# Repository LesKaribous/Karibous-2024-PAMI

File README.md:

# Karibous-2024-PAMI
Hardware pour les Petits Automates Mobiles Indépendants de la Coupe de France de Robotique 2024

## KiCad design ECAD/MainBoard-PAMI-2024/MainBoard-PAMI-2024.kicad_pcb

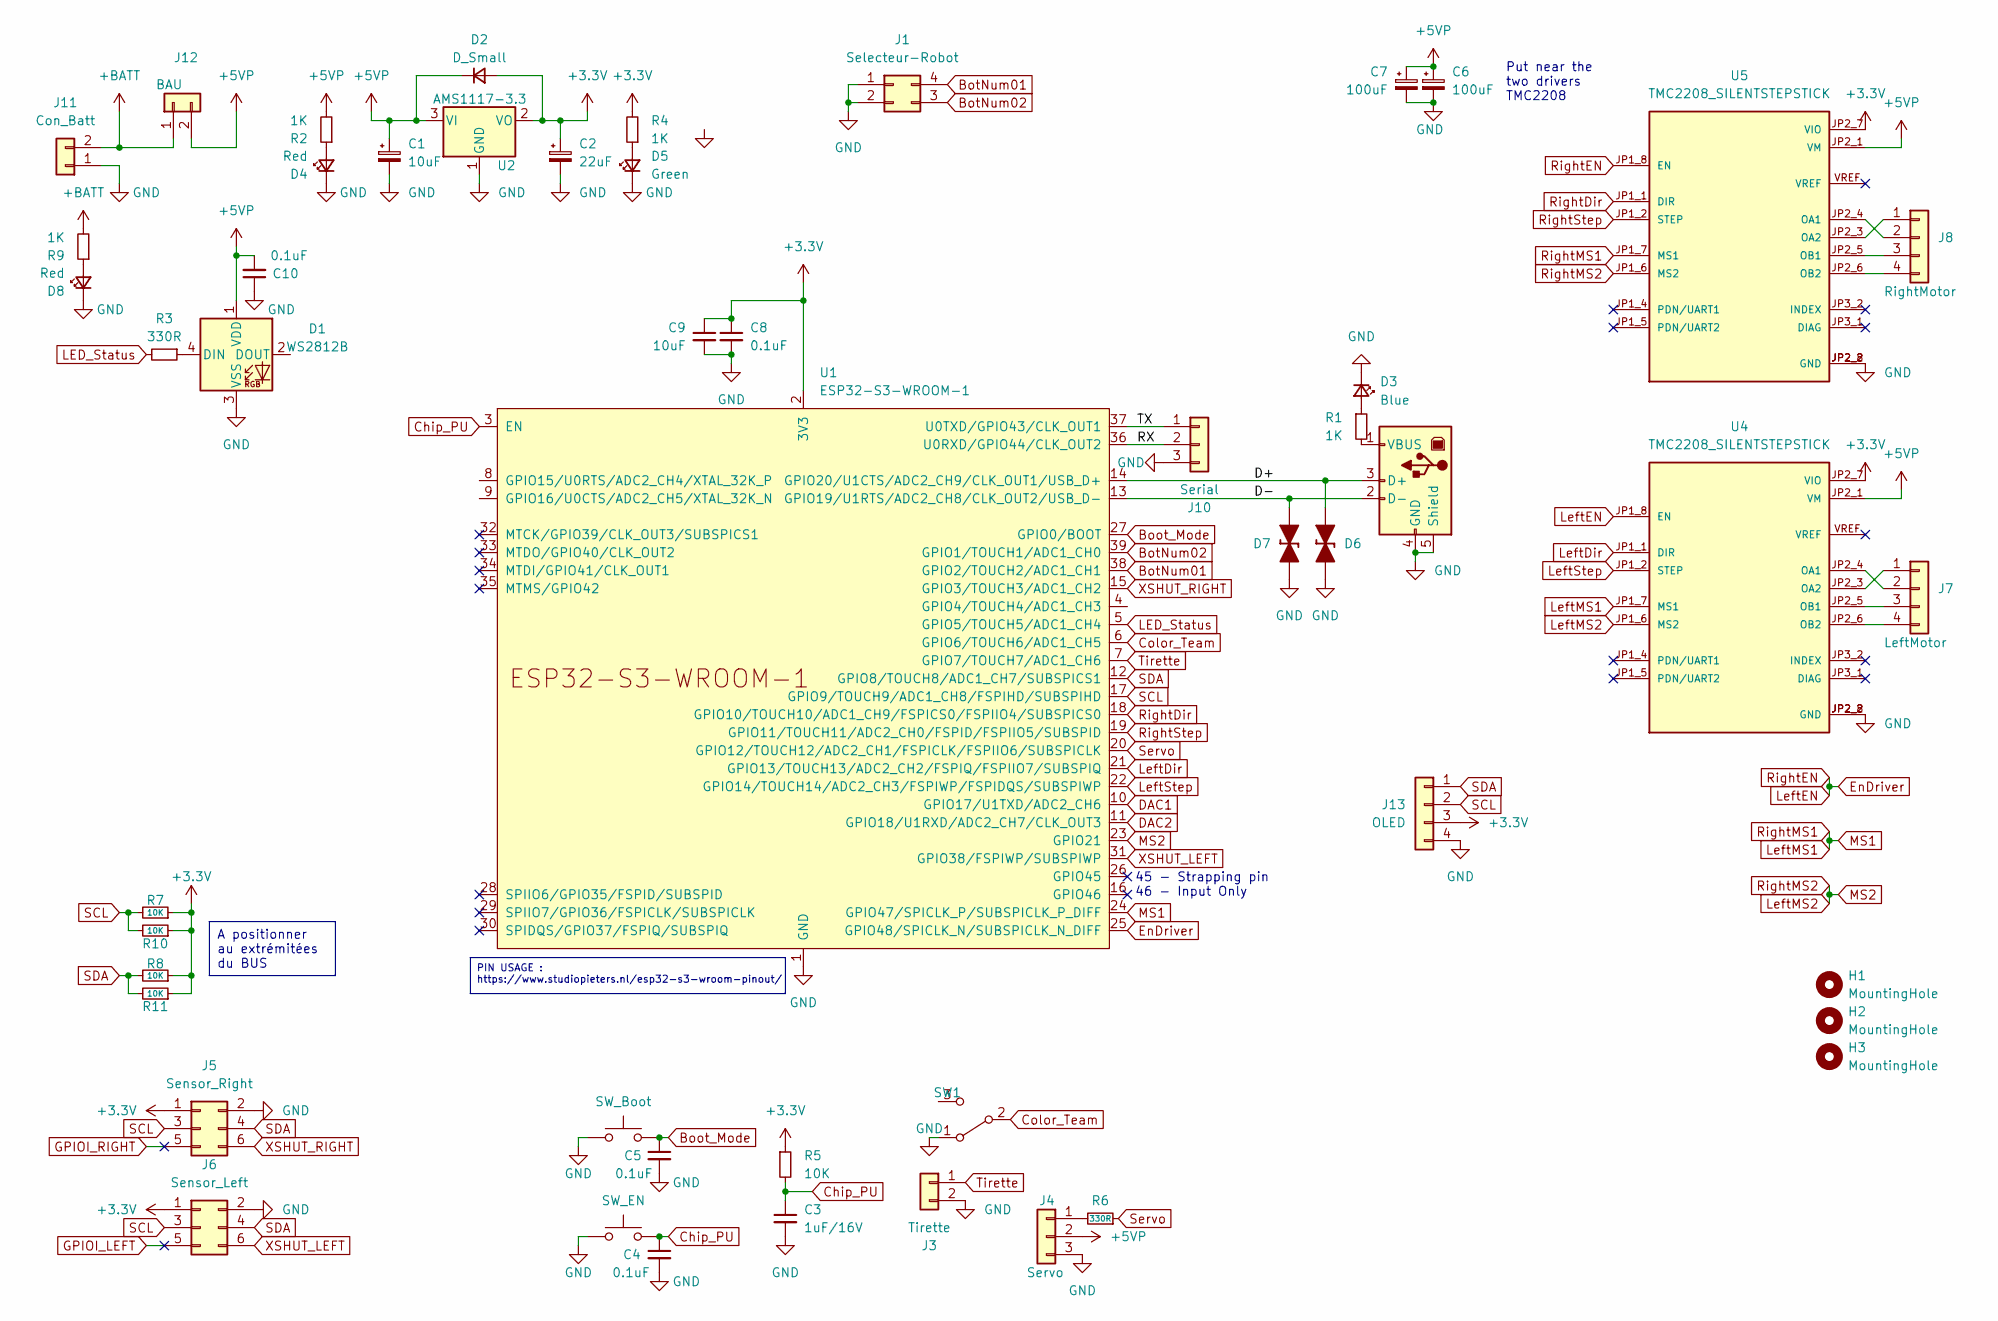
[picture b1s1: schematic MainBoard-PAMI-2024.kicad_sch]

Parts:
C1: 10uF; CP_Elec_5x5.4
C2: 22uF; CP_EIA-3528-12_Kemet-T_Pad1.50x2.35mm_HandSolder
C3: 1uF/16V; C_1206_3216Metric
C4, C5, C10: 0.1uF; C_1206_3216Metric
C6, C7: 100uF; CP_Radial_D8.0mm_P3.80mm
C8: 0.1uF; C_1206_3216Metric_Pad1.33x1.80mm_HandSolder
C9: 10uF; C_1206_3216Metric_Pad1.33x1.80mm_HandSolder
D1: WS2812B; LED_WS2812B_PLCC4_5.0x5.0mm_P3.2mm
D2: D_Small; D_SMA_Handsoldering
D3: Blue; LED_1206_3216Metric
D4, D8: Red; LED_1206_3216Metric
D5: Green; LED_1206_3216Metric
D6, D7: D_TVS_Bidirectional_Generic; D_SOD-523
H1, H2, H3: MountingHole; MountingHole_3.2mm_M3
J1: Selecteur-Robot; PinHeader_2x02_P2.54mm_Vertical
J2: USB_B; USB_B_Lumberg_2411_02_Horizontal
J3: Tirette; Molex_KK-254_AE-6410-02A_1x02_P2.54mm_Vertical
J4: Servo; PinHeader_1x03_P2.54mm_Vertical
J5: Sensor_Right; IDC-Header_2x03_P2.54mm_Vertical
J6: Sensor_Left; IDC-Header_2x03_P2.54mm_Vertical
J7: LeftMotor; PinHeader_1x04_P2.54mm_Vertical
J8: RightMotor; PinHeader_1x04_P2.54mm_Vertical
J10: Serial; PinHeader_1x03_P2.54mm_Vertical
J11: Con_Batt; AMASS_XT30U-F_1x02_P5.0mm_Vertical
J12: BAU; Molex_KK-396_A-41791-0002_1x02_P3.96mm_Vertical
J13: OLED; Molex_KK-254_AE-6410-04A_1x04_P2.54mm_Vertical
R1, R2, R4, R9: 1K; R_1206_3216Metric_Pad1.30x1.75mm_HandSolder
R3, R6: 330R; R_1206_3216Metric_Pad1.30x1.75mm_HandSolder
R5, R7, R8, R10, R11: 10K; R_1206_3216Metric_Pad1.30x1.75mm_HandSolder
SW1: SW_SPDT; SK-12D10 1P2T
SWBoot1: SW_Boot; SW_SPST_CK_RS282G05A3
SWEn1: SW_EN; SW_SPST_CK_RS282G05A3
U1: ESP32-S3-WROOM-1
U2: AMS1117-3.3; SOT-223-3_TabPin2
U4, U5: TMC2208_SILENTSTEPSTICK; MODULE_TMC2208_SILENTSTEPSTICK

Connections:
+3.3V: C2.1, C8.1, C9.1, D2.2 (A), J5.1, J6.1, J13.3, R4.2, R5.1, R7.1, R8.1, R10.1, R11.1, U1.2 (3V3), U2.2 (VO), U4.JP2_7 (VIO), U5.JP2_7 (VIO)
+5VP: C1.1, C6.1, C7.1, C10.2, D1.1 (VDD), D2.1 (K), J4.2, J12.2, R2.2, U2.3 (VI), U4.JP2_1 (VM), U5.JP2_1 (VM)
+BATT: J11.2, J12.1, R9.2
/D+: D6.2 (A), J2.3 (D+), U1.14 (GPIO20/U1CTS/ADC2_CH9/CLK_OUT1/USB_D+)
/D-: D7.2 (A), J2.2 (D-), U1.13 (GPIO19/U1RTS/ADC2_CH8/CLK_OUT2/USB_D-)
/RX: J10.2, U1.36 (U0RXD/GPIO44/CLK_OUT2)
/TX: J10.1, U1.37 (U0TXD/GPIO43/CLK_OUT1)
Boot_Mode: C5.1, SWBoot1.2, U1.27 (GPIO0/BOOT)
BotNum01: J1.4, U1.38 (GPIO2/TOUCH2/ADC1_CH1)
BotNum02: J1.3, U1.39 (GPIO1/TOUCH1/ADC1_CH0)
Chip_PU: C3.1, C4.1, R5.2, SWEn1.2, U1.3 (EN)
Color_Team: SW1.2 (B), U1.6 (GPIO6/TOUCH6/ADC1_CH5)
DAC1: U1.10 (GPIO17/U1TXD/ADC2_CH6)
DAC2: U1.11 (GPIO18/U1RXD/ADC2_CH7/CLK_OUT3)
EnDriver: U1.25 (GPIO48/SPICLK_N/SUBSPICLK_N_DIFF), U4.JP1_8 (EN), U5.JP1_8 (EN)
GND: C1.2, C2.2, C3.2, C4.2, C5.2, C6.2, C7.2, C8.2, C9.2, C10.1, D1.3 (VSS), D3.1 (K), D4.1 (K), D5.1 (K), D6.1 (K), D7.1 (K), D8.1 (K), J1.1, J1.2, J2.4 (GND), J2.5 (Shield), J3.2, J4.3, J5.2, J6.2, J10.3, J11.1, J13.4, SW1.1 (A), SWBoot1.1, SWEn1.1, U1.1 (GND), U1.40 (GND), U1.41 (GND), U2.1 (GND), U4.JP2_2 (GND), U4.JP2_8 (GND), U5.JP2_2 (GND), U5.JP2_8 (GND)
GPIOI_LEFT: J6.5
GPIOI_RIGHT: J5.5
LED_Status: R3.2, U1.5 (GPIO5/TOUCH5/ADC1_CH4)
LeftDir: U1.21 (GPIO13/TOUCH13/ADC2_CH2/FSPIQ/FSPIIO7/S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), U4.JP1_1 (DIR)
LeftMS1: U1.24 (GPIO47/SPICLK_P/SUBSPICLK_P_DIFF), U4.JP1_7 (MS1), U5.JP1_7 (MS1)
LeftMS2: U1.23 (GPIO21), U4.JP1_6 (MS2), U5.JP1_6 (MS2)
LeftStep: U1.22 (GPIO14/TOUCH14/ADC2_CH3/FSPIWP/FSPIDQS/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), U4.JP1_2 (STEP)
unnamed: D1.4 (DIN), R3.1
unnamed: D3.2 (A), R1.1
unnamed: D4.2 (A), R2.1
unnamed: D5.2 (A), R4.1
unnamed: D8.2 (A), R9.1
unnamed: J2.1 (VBUS), R1.2
unnamed: J4.1, R6.2
unnamed: J7.1, U4.JP2_3 (OA2)
unnamed: J7.2, U4.JP2_4 (OA1)
unnamed: J7.3, U4.JP2_5 (OB1)
unnamed: J7.4, U4.JP2_6 (OB2)
unnamed: J8.1, U5.JP2_3 (OA2)
unnamed: J8.2, U5.JP2_4 (OA1)
unnamed: J8.3, U5.JP2_5 (OB1)
unnamed: J8.4, U5.JP2_6 (OB2)
RightDir: U1.18 (GPIO10/TOUCH10/ADC1_CH9/FSPICS0/FSPIIO4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), U5.JP1_1 (DIR)
RightStep: U1.19 (GPIO11/TOUCH11/ADC2_CH0/FSPID/FSPIIO5/S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), U5.JP1_2 (STEP)
SCL: J5.3, J6.3, J13.2, R7.2, R10.2, U1.17 (GPIO9/TOUCH9/ADC1_CH8/FSPIHD/SUBSPIHD)
SDA: J5.4, J6.4, J13.1, R8.2, R11.2, U1.12 (GPIO8/TOUCH8/ADC1_CH7/SUBSPICS1)
Servo: R6.1, U1.20 (GPIO12/TOUCH12/ADC2_CH1/FSPICLK/FSPIIO6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)
Tirette: J3.1, U1.7 (GPIO7/TOUCH7/ADC1_CH6)
XSHUT_LEFT: J6.6, U1.31 (GPIO38/FSPIWP/SUBSPIWP)
XSHUT_RIGHT: J5.6, U1.15 (GPIO3/TOUCH3/ADC1_CH2)

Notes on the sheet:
PIN USAGE : https://www.studiopieters.nl/esp32-s3-wroom-pinout/
A positionner au extrémitées du BUS
Put near the two drivers TMC2208
45 - Strapping pin 46 - Input Only

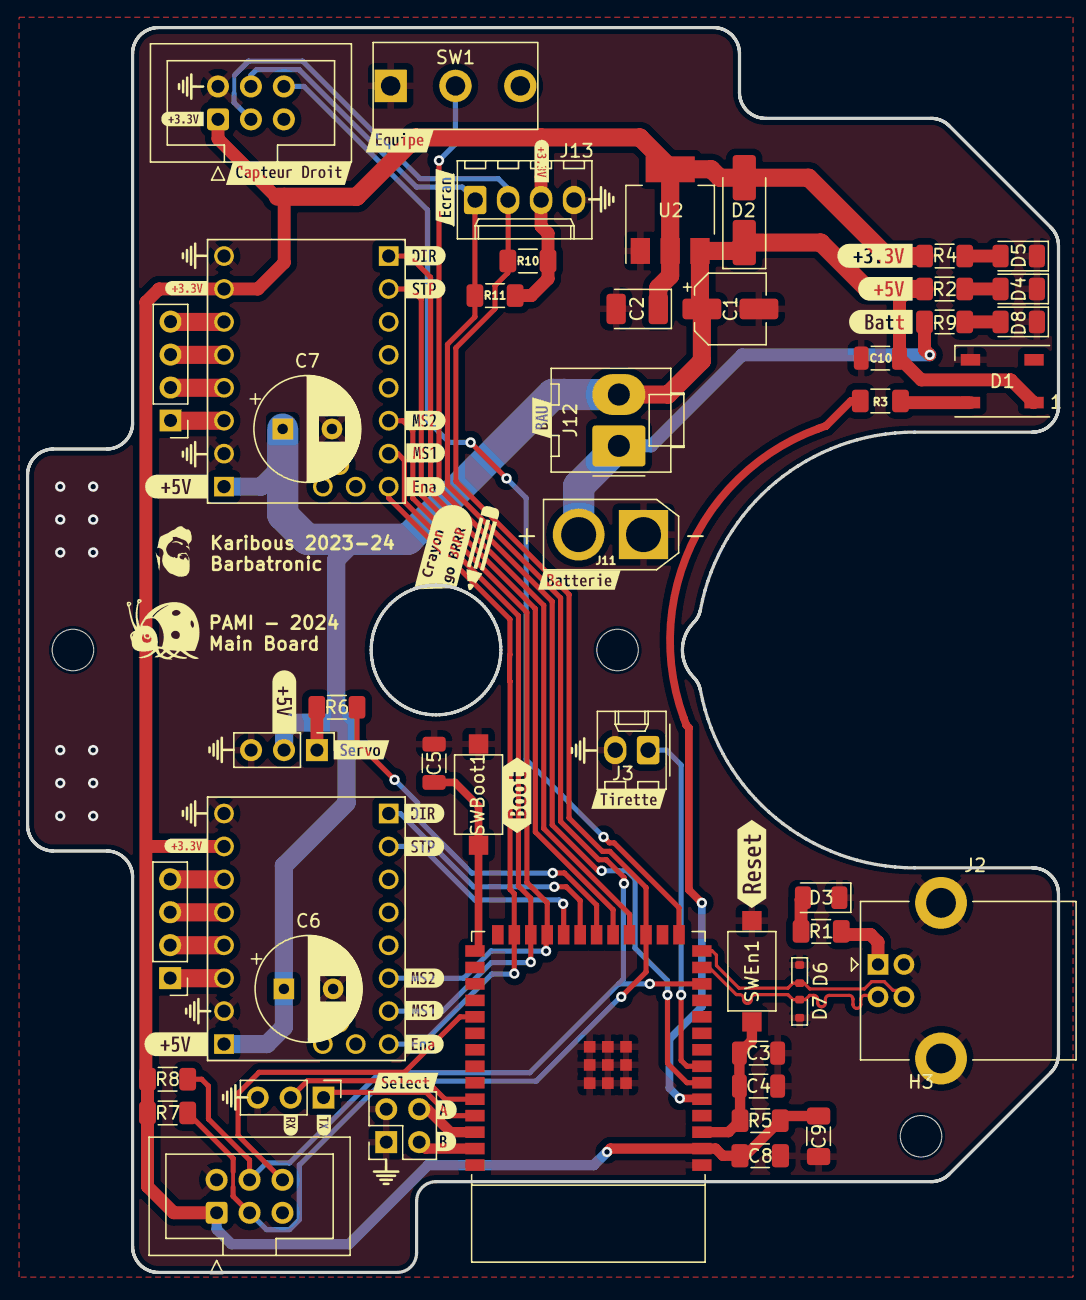
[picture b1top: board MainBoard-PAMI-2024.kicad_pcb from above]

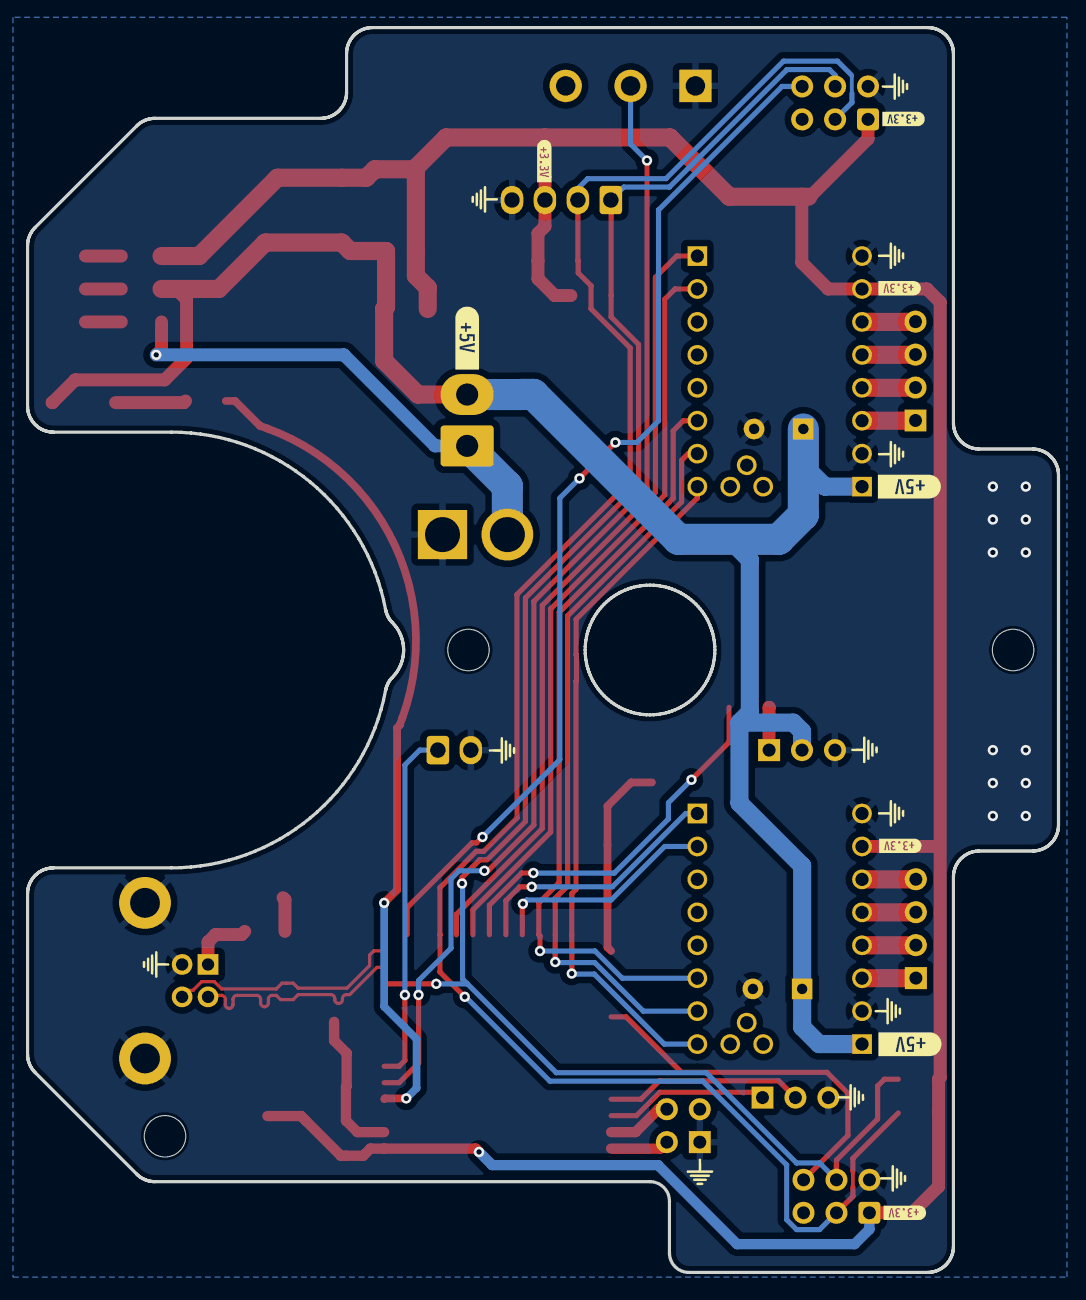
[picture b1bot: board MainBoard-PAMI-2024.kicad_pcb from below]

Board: 2 copper layers, 79.5 x 96.0 mm, 94 parts (8 on the bottom side), 42 nets.

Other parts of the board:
kibuzzard-65422A0E: G***; kibuzzard-65422A0E
kibuzzard-65422A22: G***; kibuzzard-65422A22
kibuzzard-65422AAE: G***; kibuzzard-65422AAE
kibuzzard-65422AB6: G***; kibuzzard-65422AB6
kibuzzard-65422AC7: G***; kibuzzard-65422AC7
kibuzzard-65422F57: G***; kibuzzard-65422F57
kibuzzard-654226B4, kibuzzard-654226B4#2, kibuzzard-654226B4#3, kibuzzard-654226B4#4, kibuzzard-654226B4#5, kibuzzard-654226B4#6, kibuzzard-654226B4#7, kibuzzard-654226B4#8, kibuzzard-654226B4#9: G***; kibuzzard-654226B4
kibuzzard-654229BB: G***; kibuzzard-654229BB
kibuzzard-654230EB: G***; kibuzzard-654230EB
kibuzzard-654231C8, kibuzzard-654231C8#2: G***; kibuzzard-654231C8
kibuzzard-654231D0, kibuzzard-654231D0#2: G***; kibuzzard-654231D0
kibuzzard-654231D6, kibuzzard-654231D6#2: G***; kibuzzard-654231D6
kibuzzard-654231DD, kibuzzard-654231DD#2: G***; kibuzzard-654231DD
kibuzzard-6542284D: G***; kibuzzard-6542284D
kibuzzard-6542299D: G***; kibuzzard-6542299D
kibuzzard-6542315C: G***; kibuzzard-6542315C
kibuzzard-65231966, kibuzzard-65231966#2, kibuzzard-65231966#3, kibuzzard-65231966#4, kibuzzard-65231966#5, kibuzzard-65231966#6: G***; kibuzzard-65231966
kibuzzard-65422827: G***; kibuzzard-65422827
kibuzzard-65422864: G***; kibuzzard-65422864
kibuzzard-65422975: G***; kibuzzard-65422975
kibuzzard-65422987: G***; kibuzzard-65422987
kibuzzard-65423033: G***; kibuzzard-65423033
kibuzzard-65423064: G***; kibuzzard-65423064
kibuzzard-65423077: G***; kibuzzard-65423077
kibuzzard-65423198, kibuzzard-65423198#2: G***; kibuzzard-65423198

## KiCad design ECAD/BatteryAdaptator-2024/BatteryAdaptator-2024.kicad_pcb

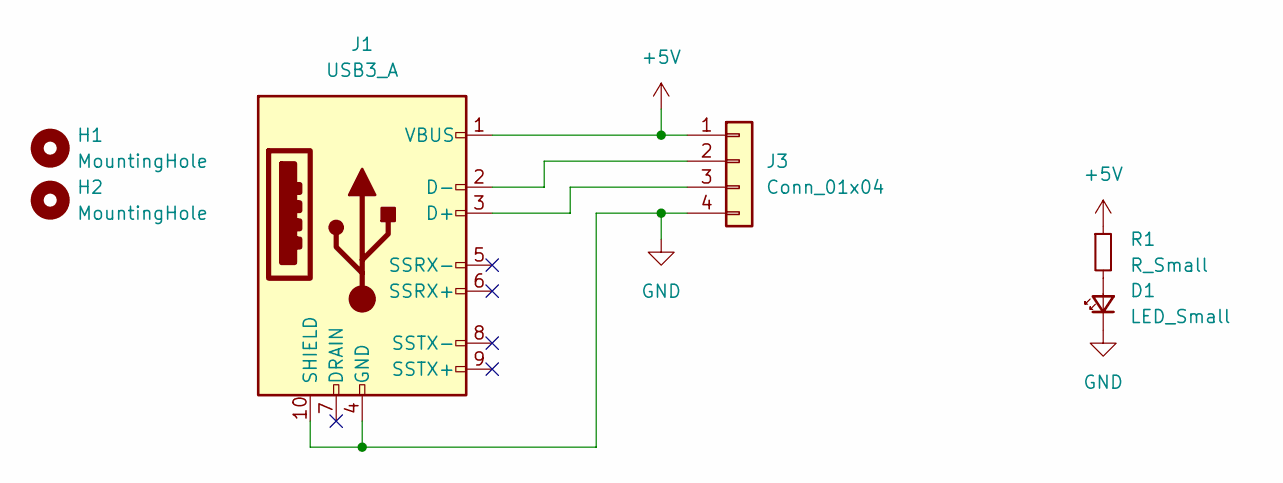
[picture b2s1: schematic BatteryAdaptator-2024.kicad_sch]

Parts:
D1: LED_Small; LED_1206_3216Metric
H1, H2: MountingHole; MountingHole_3.2mm_M3
J1: USB3_A; USB A3.0 - PowerBank XHC-005
J3: Conn_01x04; PinHeader_1x04_P2.54mm_Vertical
R1: R_Small; R_1206_3216Metric

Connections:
+5V: J1.1 (VBUS), J3.1, R1.1
GND: D1.1 (K), J1.4 (GND), J1.10 (SHIELD), J3.4
unnamed: D1.2 (A), R1.2
unnamed: J1.3 (D+), J3.3
unnamed: J1.2 (D-), J3.2

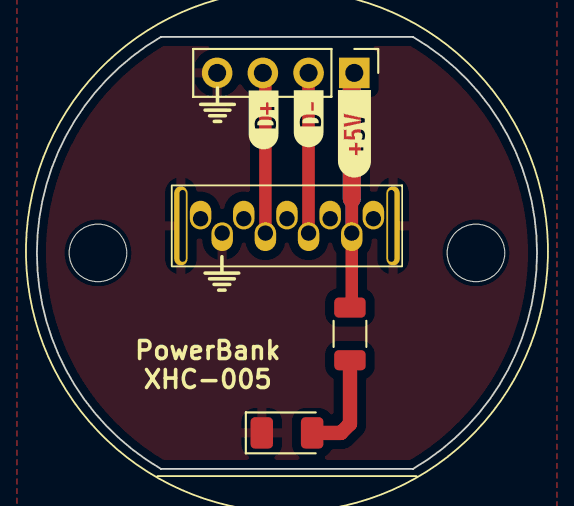
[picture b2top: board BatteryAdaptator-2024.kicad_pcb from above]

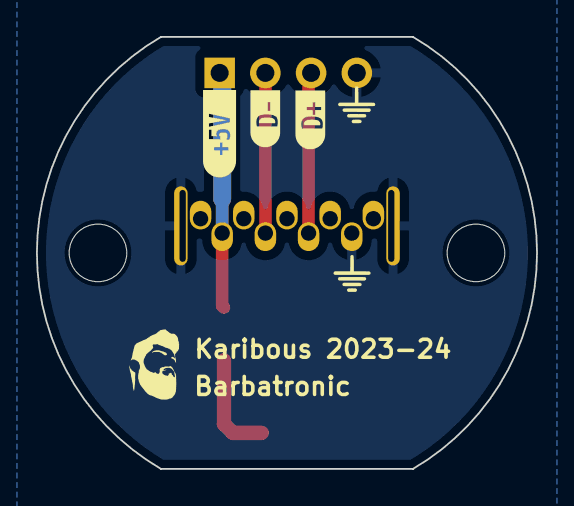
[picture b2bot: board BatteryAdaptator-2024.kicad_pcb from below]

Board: 2 copper layers, 27.8 x 24.0 mm, 12 parts (3 on the bottom side), 5 nets.

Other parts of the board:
kibuzzard-652319A9, kibuzzard-652319A9#2: G***; kibuzzard-652319A9
kibuzzard-652319B5, kibuzzard-652319B5#2: G***; kibuzzard-652319B5
kibuzzard-65231966, kibuzzard-65231966#2: G***; kibuzzard-65231966

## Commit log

2023-09-21 create file
2023-09-23 add part
2023-09-23 V2 motorisation & V1 carter
2023-09-24 laser and tirette (live 175)
2023-09-25 add servo
2023-09-27 add hole for the Head
2023-09-27 add VL53L0X sensor
2023-09-27 first test with PCB cut
2023-09-29 Modify Cut / Add components
    Add :
    - Connectors
    - new Cut
    - Regulator
    - LEDs
    - USB
2023-09-29 Modify PCB - Add hole for Servo
2023-09-30 add rod on wings
2023-10-01 Add parts
    - Add head
    - Add eyes
    - Add BAU extender
    - add screws on the wings
    - fix top position
2023-10-01 add buzzer
2023-10-01 add pen hole and opto sensor
2023-10-01 Hole for the pencil
2023-10-08 update live 177
    - Conn USB lib
    - Conn USB 3D
    - Silkscreen
    - Dimensions
2023-10-08 Added USB PCB connector
2023-10-21 Add insert and screw for PCB
2023-10-21 minor adjustement
2023-10-21 add TMC2208 reorgnise components
2023-10-22 add capacitor for ESP32
2023-10-25 update view
2023-10-30 Create Dissipator for TMC
2023-10-30 New version
    - Wire pins
    - Add PCB way
    - Change Cutout
    - Update 3D
2023-10-30 create 3D PCB and components
2023-10-30 Change Cutout
2023-10-30 Add new PCB
2023-11-01 First routing
2023-11-01 New PCB (Routing)
2023-11-01 Fix XT60 (Histo t'as vu)
2023-11-01 Silkscreen
2023-11-01 New PCB version
2023-11-02 fix cutout
2023-11-27 Fix top robot and add pad
2023-12-13 Create DummyPAMI.FCStd
    Create pami for homologation.
2023-12-13 clean up
2023-12-13 update PAMI - Sensor orientation
    - Add diffuse acrylic for RGB led
    - Change switch length
    - Change sensor orientation (main modification)
2023-12-13 First upload - All tests OK
    - Testing firmware
    - Simple functions
    - Arduino IDE file -> should be move to PIO soon
    - All the main function of the robot works correctly
2023-12-14 change firmware to PIO
2023-12-16 Update wings and rapid screw position
2023-12-16 clean test code
2023-12-16 clean arborescence
2023-12-17 wip motion
2023-12-17 AccelStepper -> TeensyStep (fork ESP32Step)
2023-12-17 Antenna test (WIP)
2023-12-17 change angle conversion
2023-12-17 add oled on wing
2023-12-17 change oled orientation
2023-12-18 fix slow oled
    delete delay(1000) -> test forget
2023-12-18 WIP - move and polar move
2023-12-19 update LCD refresh
2023-12-19 reverse - Go for AccelStepper 😥
2023-12-20 Implement task to update motors
2024-02-02 add info on cap boot
2024-02-02 minor fix and horn
2024-02-03 try to fix the non-reseting issue with PAMI 2 and 3
2024-02-03 implement number of the robots
2024-02-03 add bot number and fancy SplashScreen
2024-02-03 update Antennas - Remove Task
2024-02-04 minor view fix
2024-02-04 add Paring screen
2024-02-04 add espNow init
2024-02-04 add conditions for pairing
2024-02-05 add ESPNow synchro launch - WIP
2024-02-27 upstream change before switch to new repository
2024-02-27 New tool for datum
2024-03-27 minor fix
2024-04-04 Remove Pairing - Yellow datum and match
2024-04-07 Add sensors and match time - READY FOR BELGIUM !!!!
2024-04-07 V2 - PETG
2024-05-01 new tirette
2025-05-25 WIP Drawing PAMI
2025-05-25 WIP drawing
